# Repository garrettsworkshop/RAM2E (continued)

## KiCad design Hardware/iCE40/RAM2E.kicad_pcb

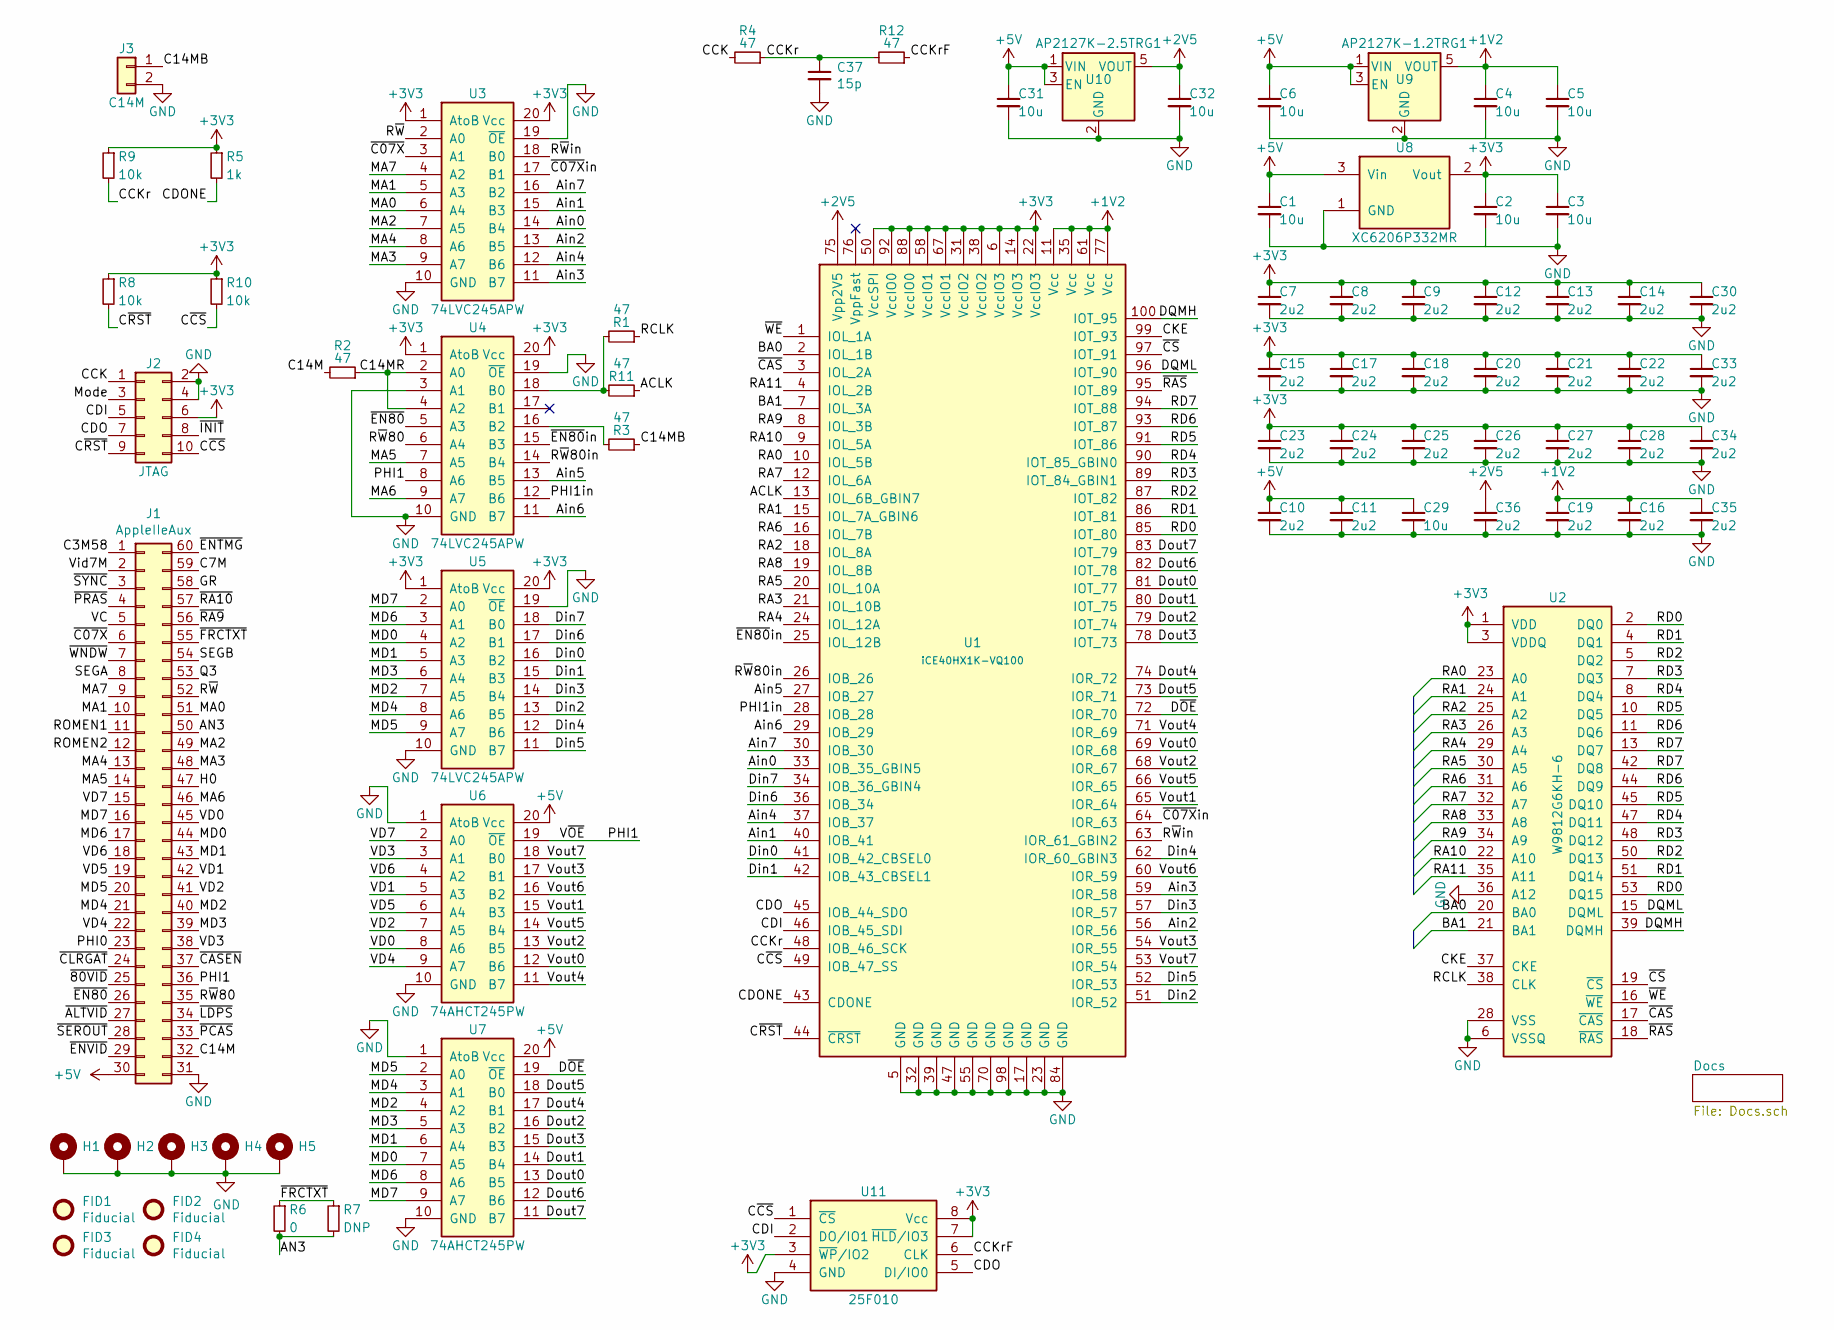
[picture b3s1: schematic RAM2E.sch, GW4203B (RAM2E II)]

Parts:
C1, C2, C3, C4, C5, C6, C29, C31, C32: 10u; C_0805; Mfg. Part Numbers Samsung CL21A106KAYNNNE; LCSC Part C15850
C7, C8, C9, C10, C11, C12, C13, C14, C15, C16, C17, C18, C19, C20, C21, C22, C23, C24, C25, C26, C27, C28, C30, C33, C34, C35, C36: 2u2; C_0603; Mfg. Part Numbers Samsung CL10A225KO8NNNC; LCSC Part C23630
C37: 15p; C_0603
FID1, FID2, FID3, FID4: Fiducial
H1, H2, H3, H4: PasteHole_1.152mm_NPTH
H5: PasteHole_1.1mm_PTH
J1: AppleIIeAux; AppleIIeAux_Edge
J2: JTAG; TC2050
J3: C14M; PinHeader_1x02_P2.54mm_Vertical
R1, R2, R3, R4, R11, R12: 47; R_0603; Mfg. Part Numbers Uniroyal 0603WAF470JT5E; LCSC Part C23182
R5: 1k; R_0603; Mfg. Part Numbers Uniroyal 0805W8F2202T5E; LCSC Part C17560
R6: 0; R_0805; Mfg. Part Numbers Uniroyal 0805W8F2202T5E; LCSC Part C17477
R7: DNP; R_0805
R8, R9, R10: 10k; R_0603; Mfg. Part Numbers Uniroyal 0805W8F2202T5E; LCSC Part C17560
U1: iCE40HX1K-VQ100; TQFP-100_14x14mm_P0.5mm
U2: W9812G6KH-6; TSOP-II-54_22.2x10.16mm_P0.8mm; Mfg. Part Numbers Winbond W9812G6KH-6, Winbond W9812G6KH-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; LCSC Part C62379
U3, U4, U5: 74LVC245APW; TSSOP-20_4.4x6.5mm_P0.65mm; Mfg. Part Numbers NXP 74LVC245APW, TI SN74LVC245APW; LCSC Part C6082
U6, U7: 74AHCT245PW; TSSOP-20_4.4x6.5mm_P0.65mm; Mfg. Part Numbers NXP 74AHCT245PW, TI SN74AHCT245PW; LCSC Part C173388
U8: XC6206P332MR; SOT-23; Mfg. Part Numbers Torex XC6206P332MR; LCSC Part C5446
U9: AP2127K-1.2TRG1; SOT-23-5
U10: AP2127K-2.5TRG1; SOT-23-5
U11: 25F010; SOIC-8_5.3mm

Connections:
+1V2: C4.1, C5.1, C16.1, C19.1, C35.1, U1.11 (Vcc), U1.35 (Vcc), U1.61 (Vcc), U1.77 (Vcc), U9.5 (VOUT)
+2V5: C32.1, C36.1, U1.75 (Vpp2V5), U10.5 (VOUT)
+3V3: C2.1, C3.1, C7.1, C8.1, C9.1, C12.1, C13.1, C14.1, C15.1, C17.1, C18.1, C20.1, C21.1, C22.1, C23.1, C24.1, C25.1, C26.1, C27.1, C28.1, C30.1, C33.1, C34.1, J2.6, R5.1, R8.1, R9.1, R10.1, U1.6 (VccIO3), U1.14 (VccIO3), U1.22 (VccIO3), U1.31 (VccIO2), U1.38 (VccIO2), U1.50 (VccSPI), U1.58 (VccIO1), U1.67 (VccIO1), U1.88 (VccIO0), U1.92 (VccIO0), U2.1 (VDD), U2.3 (VDDQ), U2.9 (VDDQ), U2.14 (VDD), U2.27 (VDD), U2.43 (VDDQ), U2.49 (VDDQ), U3.1 (AtoB), U3.20 (Vcc), U4.1 (AtoB), U4.20 (Vcc), U5.1 (AtoB), U5.20 (Vcc), U8.2 (Vout), U11.3 (~WP~/IO2), U11.7 (~HLD~/IO3), U11.8 (Vcc); also elsewhere on the board
+5V: C1.1, C6.1, C10.1, C11.1, C29.1, C31.1, J1.30, U6.20 (Vcc), U7.20 (Vcc), U8.3 (Vin), U9.1 (VIN), U9.3 (EN), U10.1 (VIN), U10.3 (EN)
/ACLK: R11.1, U1.13 (IOL_6B_GBIN7)
/AN3: J1.50, R6.2, R7.2
/Ain0: U1.33 (IOB_35_GBIN5), U3.14 (B4)
/Ain1: U1.40 (IOB_41), U3.15 (B3)
/Ain2: U1.56 (IOR_56), U3.13 (B5)
/Ain3: U1.59 (IOR_58), U3.11 (B7)
/Ain4: U1.37 (IOB_37), U3.12 (B6)
/Ain5: U1.27 (IOB_27), U4.13 (B5)
/Ain6: U1.29 (IOB_29), U4.11 (B7)
/Ain7: U1.30 (IOB_30), U3.16 (B2)
/BA0: U1.2 (IOL_1B), U2.20 (BA0)
/BA1: U1.7 (IOL_3A), U2.21 (BA1)
/C3M58: J1.1
/C7M: J1.59
/C14M: J1.32, R2.2
/C14MB: J3.1, R3.1
/C14MR: R2.1, U4.2 (A0), U4.4 (A2)
/CCK: J2.1, R4.2
/CCKr: C37.1, R4.1, R9.2, R12.2, U1.48 (IOB_46_SCK)
/CCKrF: R12.1, U11.6 (CLK)
/CDI: J2.5, U1.46 (IOB_45_SDI), U11.2 (DO/IO1)
/CDO: J2.7, U1.45 (IOB_44_SDO), U11.5 (DI/IO0)
/CDONE: R5.2, U1.43 (CDONE)
/CKE: U1.99 (IOT_93), U2.37 (CKE)
/C~CS~: J2.10, R10.2, U1.49 (IOB_47_SS), U11.1 (~CS~)
/C~RST~: J2.9, R8.2, U1.44 (~CRST~)
/DQMH: U1.100 (IOT_95), U2.39 (DQMH)
/DQML: U1.96 (IOT_90), U2.15 (DQML)
/Din0: U1.41 (IOB_42_CBSEL0), U5.16 (B2)
/Din1: U1.42 (IOB_43_CBSEL1), U5.15 (B3)
/Din2: U1.51 (IOR_52), U5.13 (B5)
/Din3: U1.57 (IOR_57), U5.14 (B4)
/Din4: U1.62 (IOR_60_GBIN3), U5.12 (B6)
/Din5: U1.52 (IOR_53), U5.11 (B7)
/Din6: U1.36 (IOB_34), U5.17 (B1)
/Din7: U1.34 (IOB_36_GBIN4), U5.18 (B0)
/Dout0: U1.81 (IOT_77), U7.13 (B5)
/Dout1: U1.80 (IOT_75), U7.14 (B4)
/Dout2: U1.79 (IOT_74), U7.16 (B2)
/Dout3: U1.78 (IOT_73), U7.15 (B3)
/Dout4: U1.74 (IOR_72), U7.17 (B1)
/Dout5: U1.73 (IOR_71), U7.18 (B0)
/Dout6: U1.82 (IOT_78), U7.12 (B6)
/Dout7: U1.83 (IOT_79), U7.11 (B7)
/GR: J1.58
/H0: J1.47
/MA0: J1.51, U3.6 (A4)
/MA1: J1.10, U3.5 (A3)
/MA2: J1.49, U3.7 (A5)
/MA3: J1.48, U3.9 (A7)
/MA4: J1.13, U3.8 (A6)
/MA5: J1.14, U4.7 (A5)
/MA6: J1.46, U4.9 (A7)
/MA7: J1.9, U3.4 (A2)
/MD0: J1.44, U5.4 (A2), U7.7 (A5)
/MD1: J1.43, U5.5 (A3), U7.6 (A4)
/MD2: J1.40, U5.7 (A5), U7.4 (A2)
/MD3: J1.39, U5.6 (A4), U7.5 (A3)
/MD4: J1.21, U5.8 (A6), U7.3 (A1)
/MD5: J1.20, U5.9 (A7), U7.2 (A0)
/MD6: J1.17, U5.3 (A1), U7.8 (A6)
/MD7: J1.16, U5.2 (A0), U7.9 (A7)
/Mode: J2.3
/PHI0: J1.23
/PHI1: J1.36, U4.8 (A6), U6.19 (~OE~)
/PHI1in: U1.28 (IOB_28), U4.12 (B6)
/Q3: J1.53
/RA0: U1.10 (IOL_5B), U2.23 (A0)
/RA1: U1.15 (IOL_7A_GBIN6), U2.24 (A1)
/RA2: U1.18 (IOL_8A), U2.25 (A2)
/RA3: U1.21 (IOL_10B), U2.26 (A3)
/RA4: U1.24 (IOL_12A), U2.29 (A4)
/RA5: U1.20 (IOL_10A), U2.30 (A5)
/RA6: U1.16 (IOL_7B), U2.31 (A6)
/RA7: U1.12 (IOL_6A), U2.32 (A7)
/RA8: U1.19 (IOL_8B), U2.33 (A8)
/RA9: U1.8 (IOL_3B), U2.34 (A9)
/RA10: U1.9 (IOL_5A), U2.22 (A10)
/RA11: U1.4 (IOL_2B), U2.35 (A11)
/RCLK: R1.1, U2.38 (CLK)
/RD0: U1.85 (IOT_80), U2.2 (DQ0), U2.53 (DQ15)
/RD1: U1.86 (IOT_81), U2.4 (DQ1), U2.51 (DQ14)
/RD2: U1.87 (IOT_82), U2.5 (DQ2), U2.50 (DQ13)
/RD3: U1.89 (IOT_84_GBIN1), U2.7 (DQ3), U2.48 (DQ12)
/RD4: U1.90 (IOT_85_GBIN0), U2.8 (DQ4), U2.47 (DQ11)
/RD5: U1.91 (IOT_86), U2.10 (DQ5), U2.45 (DQ10)
/RD6: U1.93 (IOT_87), U2.11 (DQ6), U2.44 (DQ9)
/RD7: U1.94 (IOT_88), U2.13 (DQ7), U2.42 (DQ8)
/ROMEN1: J1.11
/ROMEN2: J1.12
/R~W~: J1.52, U3.2 (A0)
/R~W~80: J1.35, U4.6 (A4); also elsewhere on the board
/R~W~80in: U1.26 (IOB_26), U4.14 (B4)
/R~W~in: U1.63 (IOR_61_GBIN2), U3.18 (B0)
/SEGA: J1.8
/SEGB: J1.54
/VC: J1.5
/VD0: J1.45, U6.8 (A6)
/VD1: J1.42, U6.5 (A3)
/VD2: J1.41, U6.7 (A5)
/VD3: J1.38, U6.3 (A1)
/VD4: J1.22, U6.9 (A7)
/VD5: J1.19, U6.6 (A4)
/VD6: J1.18, U6.4 (A2)
/VD7: J1.15, U6.2 (A0)
/Vid7M: J1.2
/Vout0: U1.69 (IOR_68), U6.12 (B6)
/Vout1: U1.65 (IOR_64), U6.15 (B3)
/Vout2: U1.68 (IOR_67), U6.13 (B5)
/Vout3: U1.54 (IOR_55), U6.17 (B1)
/Vout4: U1.71 (IOR_69), U6.11 (B7)
/Vout5: U1.66 (IOR_65), U6.14 (B4)
/Vout6: U1.60 (IOR_59), U6.16 (B2)
/Vout7: U1.53 (IOR_54), U6.18 (B0)
/~80VID~: J1.25
/~ALTVID~: J1.27
/~C07X~: J1.6, U3.3 (A1)
/~C07X~in: U1.64 (IOR_63), U3.17 (B1)
/~CASEN~: J1.37
/~CAS~: U1.3 (IOL_2A), U2.17 (~CAS~)
/~CLRGAT~: J1.24
/~CS~: U1.97 (IOT_91), U2.19 (~CS~)
/~EN80~: J1.26, U4.5 (A3); also elsewhere on the board
/~EN80~in: U1.25 (IOL_12B), U4.15 (B3)
/~ENTMG~: J1.60
/~ENVID~: J1.29
/~FRCTXT~: J1.55, R6.1, R7.1
/~INIT~: J2.8
/~LDPS~: J1.34
/~PCAS~: J1.33
/~PRAS~: J1.4
/~RA9~: J1.56
/~RA10~: J1.57
/~RAS~: U1.95 (IOT_89), U2.18 (~RAS~)
/~SEROUT~: J1.28
/~SYNC~: J1.3
/~WE~: U1.1 (IOL_1A), U2.16 (~WE~)
/~WNDW~: J1.7
GND: C1.2, C2.2, C3.2, C4.2, C5.2, C6.2, C7.2, C8.2, C9.2, C10.2, C11.2, C12.2, C13.2, C14.2, C15.2, C16.2, C17.2, C18.2, C19.2, C20.2, C21.2, C22.2, C23.2, C24.2, C25.2, C26.2, C27.2, C28.2, C29.2, C30.2, C31.2, C32.2, C33.2, C34.2, C35.2, C36.2, C37.2, H1.1, H2.1, H3.1, H4.1, H5.1, J1.31, J2.2, J2.4, J3.2, U1.5 (GND), U1.17 (GND), U1.23 (GND), U1.32 (GND), U1.39 (GND), U1.47 (GND), U1.55 (GND), U1.70 (GND), U1.84 (GND), U1.98 (GND), U2.6 (VSSQ), U2.12 (VSSQ), U2.28 (VSS), U2.36 (A12), U2.41 (VSS), U2.46 (VSSQ), U2.52 (VSSQ), U2.54 (VSS), U3.10 (GND), U3.19 (~OE~), U4.3 (A1), U4.10 (GND), U4.19 (~OE~), U5.10 (GND), U5.19 (~OE~), U6.1 (AtoB), U6.10 (GND), U7.1 (AtoB), U7.10 (GND), U8.1 (GND), U9.2 (GND), U10.2 (GND), U11.4 (GND); also elsewhere on the board
unnamed: R1.2, R11.2, U4.18 (B0)
unnamed: R3.2, U4.16 (B2)

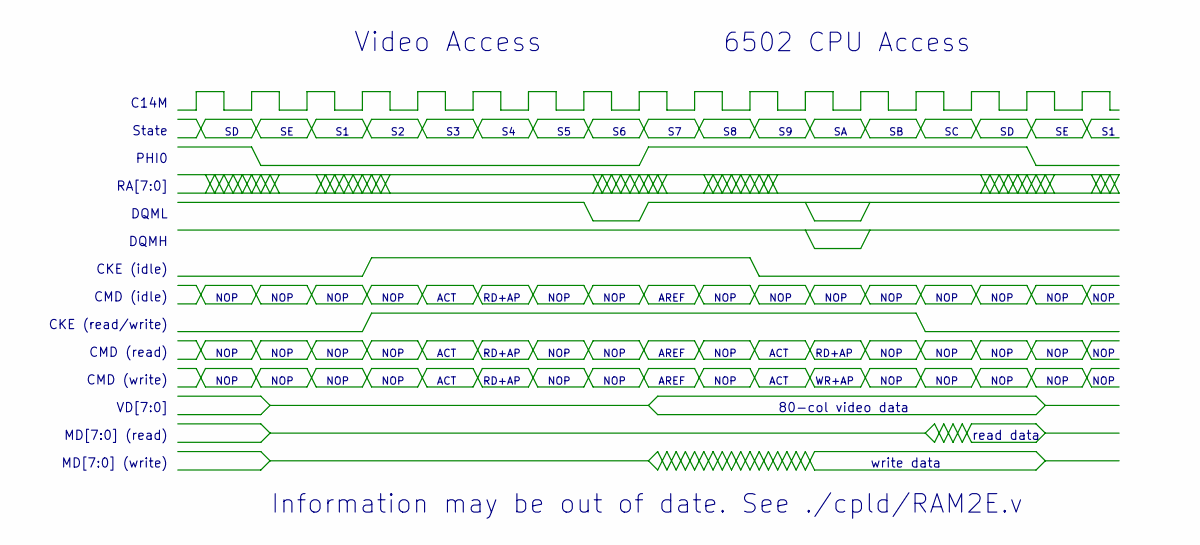
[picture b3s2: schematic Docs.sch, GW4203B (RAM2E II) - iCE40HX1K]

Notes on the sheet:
Video Access
6502 CPU Access
PHI0
C14M
RA[7:0]
State
CKE (read/write)
NOP
RD+AP
ACT
WR+AP
CMD (write)
CMD (read)
DQML
VD[7:0]
MD[7:0] (read)
MD[7:0] (write)
Information may be out of date. See ./cpld/RAM2E.v
read data
write data
80-col video data
CMD (idle)
CKE (idle)
AREF
DQMH

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
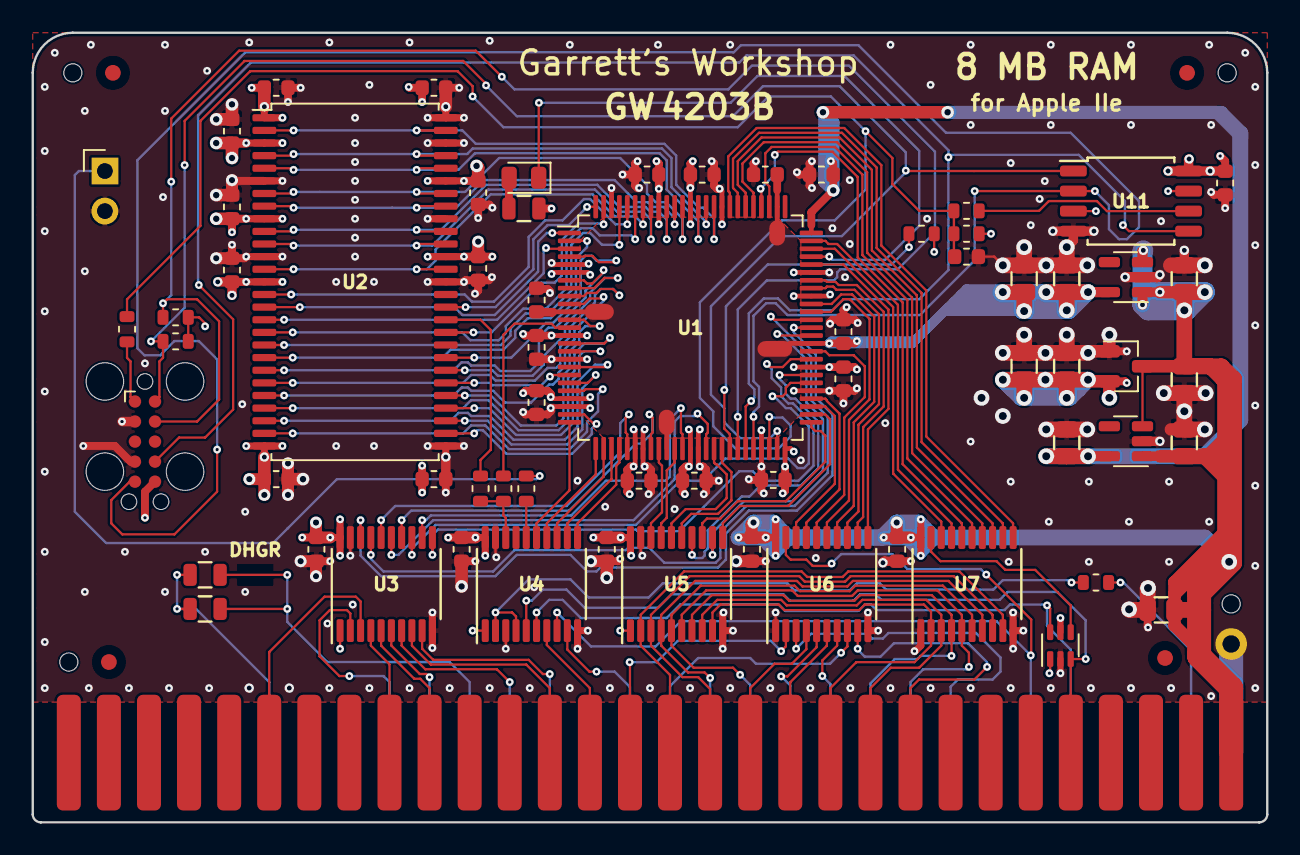
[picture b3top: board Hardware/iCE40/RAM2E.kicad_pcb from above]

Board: 4 copper layers, 78.2 x 50.0 mm, 75 parts (0 on the bottom side), 120 nets.

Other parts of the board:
D1: White; LED_0805
R13: 180; R_0805
U12: 74LVC1G97; SOT-363

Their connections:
+3V3: R13.2, U12.1, U12.5; also elsewhere on the board
/R~W~80: U12.6; also elsewhere on the board
/~EN80~: U12.3; also elsewhere on the board
GND: U12.2; also elsewhere on the board
unnamed: D1.2, R13.1

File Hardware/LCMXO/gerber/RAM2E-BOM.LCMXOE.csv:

Reference, Quantity, Value, Footprint, Datasheet, LCSC Part, Mfg. Part Numbers, Notes
C7 C8 C9 C10 C11 C12 C13 C14 C15 C16 C17 C18 C19 C20 C21 C22 C23 C24 C25 C26 C27 C28 C30 ,23,2u2,stdpads:C_0603,,C23630,Samsung CL10A225KO8NNNC,"10V or higher. Any manufacturer's part is acceptable but Samsung, Murata, Yageo preferred."
C1 C2 C3 C4 C5 C6 C29 ,7,10u,stdpads:C_0805,,C15850,Samsung CL21A106KAYNNNE,"10V or higher. Any manufacturer's part is acceptable but Samsung, Murata, Yageo preferred."
C31 ,1,15p,stdpads:C_0603,,,,"10V or higher. Any manufacturer's part is acceptable but Samsung, Murata, Yageo preferred."
D1 ,1,White,stdpads:LED_0805,,C34499,Hubei Kento C34499,Any manufacturer's part is acceptable.
FID1 FID2 FID3 FID4 ,4,Fiducial,stdpads:Fiducial,,,,DNP - SMT vision system fiducial
H1 H2 H3 H4 ,4, ,stdpads:PasteHole_1.152mm_NPTH,,,,DNP - mounting hole for solder paste printing
H5 ,1, ,stdpads:PasteHole_1.1mm_PTH,,,,DNP - mounting hole
J1 ,1,AppleIIeAux,stdpads:AppleIIeAux_Edge,,,,DNP - edge connector
J2 ,1,JTAG,stdpads:TC2050,,,,DNP - test pad connector
J3 ,1,C14M,Connector_PinHeader_2.54mm:PinHeader_1x02_P2.54mm_Vertical,,,,DNP
R1 ,1,DNP,stdpads:R_0805,,,,
R10 ,1,180,stdpads:R_0805,,C25270,Uniroyal 0805W8F1800T5E,Any manufacturer's part is acceptable.
R2 R3 R4 R5 R8 ,5,47,stdpads:R_0603,,C23182,Uniroyal 0603WAF470JT5E,Any manufacturer's part is acceptable.
R6 ,1,0,stdpads:R_0805,,C17477,Uniroyal 0805W8F0000T5E,Any manufacturer's part is acceptable.
R7 ,1,DNP,stdpads:R_0805,,,,
R9 ,1,10k,stdpads:R_0603,,C25804,Uniroyal 0603WAF1002T5E,Any manufacturer's part is acceptable.
U1 ,1,LCMXO256-TN100,stdpads:TQFP-100_14x14mm_P0.5mm,,C1550734,"Lattice LCMXO256E-3TN100C, Lattice LCMXO256E-4TN100C, Lattice LCMXO256E-5TN100C, Lattice LCMXO256E-3TN100I, Lattice LCMXO256E-4TN100I, Lattice LCMXO640E-3TN100C, Lattice LCMXO640E-4TN100C, Lattice LCMXO640E-5TN100C, Lattice LCMXO640E-3TN100I, Lattice LCMXO640E-4TN100I",
U11 ,1,25F010,stdpads:SOIC-8_5.3mm,,C2687406,"Zetta ZD25WD20BTIGT, Adesto AT25SF081-SSHD, Winbond W25X20CLSNIG",Most SPI flash in SOIC-8 (3.9mm / 150 mil width) package is acceptable.
U2 ,1,W9812G6KH-6,stdpads:TSOP-II-54_22.2x10.16mm_P0.8mm,,C62379,"Winbond W9812G6KH-6, Winbond W9812G6KH-6I, Winbond W9825G6KH-6, Winbond W9825G6KH-6I, ISSI IS42S16160J-6TL, ISSI IS42S16160J-6TLI, Micron MT48LC16M16A2P-6A :G, Micron MT48LC16M16A2P-6A IT:G",Most 166 MHz 128/256 Mbit x16 SDRAM is acceptable.
U3 U4 U5 ,3,74LVC245APW,stdpads:TSSOP-20_4.4x6.5mm_P0.65mm,,C6082,"NXP 74LVC245APW, TI SN74LVC245APW, NXP 74AHC245PW, NXP 74AHC245APW, TI SN74AHC245PW",Most 74LVC245 or 74AHC245 in TSSOP-20 package is acceptable.
U6 U7 ,2,74AHCT245PW,stdpads:TSSOP-20_4.4x6.5mm_P0.65mm,,C173388,"NXP 74AHCT245PW, NXP 74AHCT245APW, TI SN74AHCT245PW",Most 74AHCT245 in TSSOP-20 package is acceptable.
U8 ,1,XC6206P332MR,stdpads:SOT-23,,C5446,Torex XC6206P332MR,Most 3.3V regulator in SOT-23 package is acceptable.
U9 ,1,AP2127K-1.2TRG1,stdpads:SOT-23-5,,C151376,"Diodes AP2127K-1.2TRG1, Torex XC6228D122VR",Most 1.2V regulator in SOT-23-5 package is acceptable.

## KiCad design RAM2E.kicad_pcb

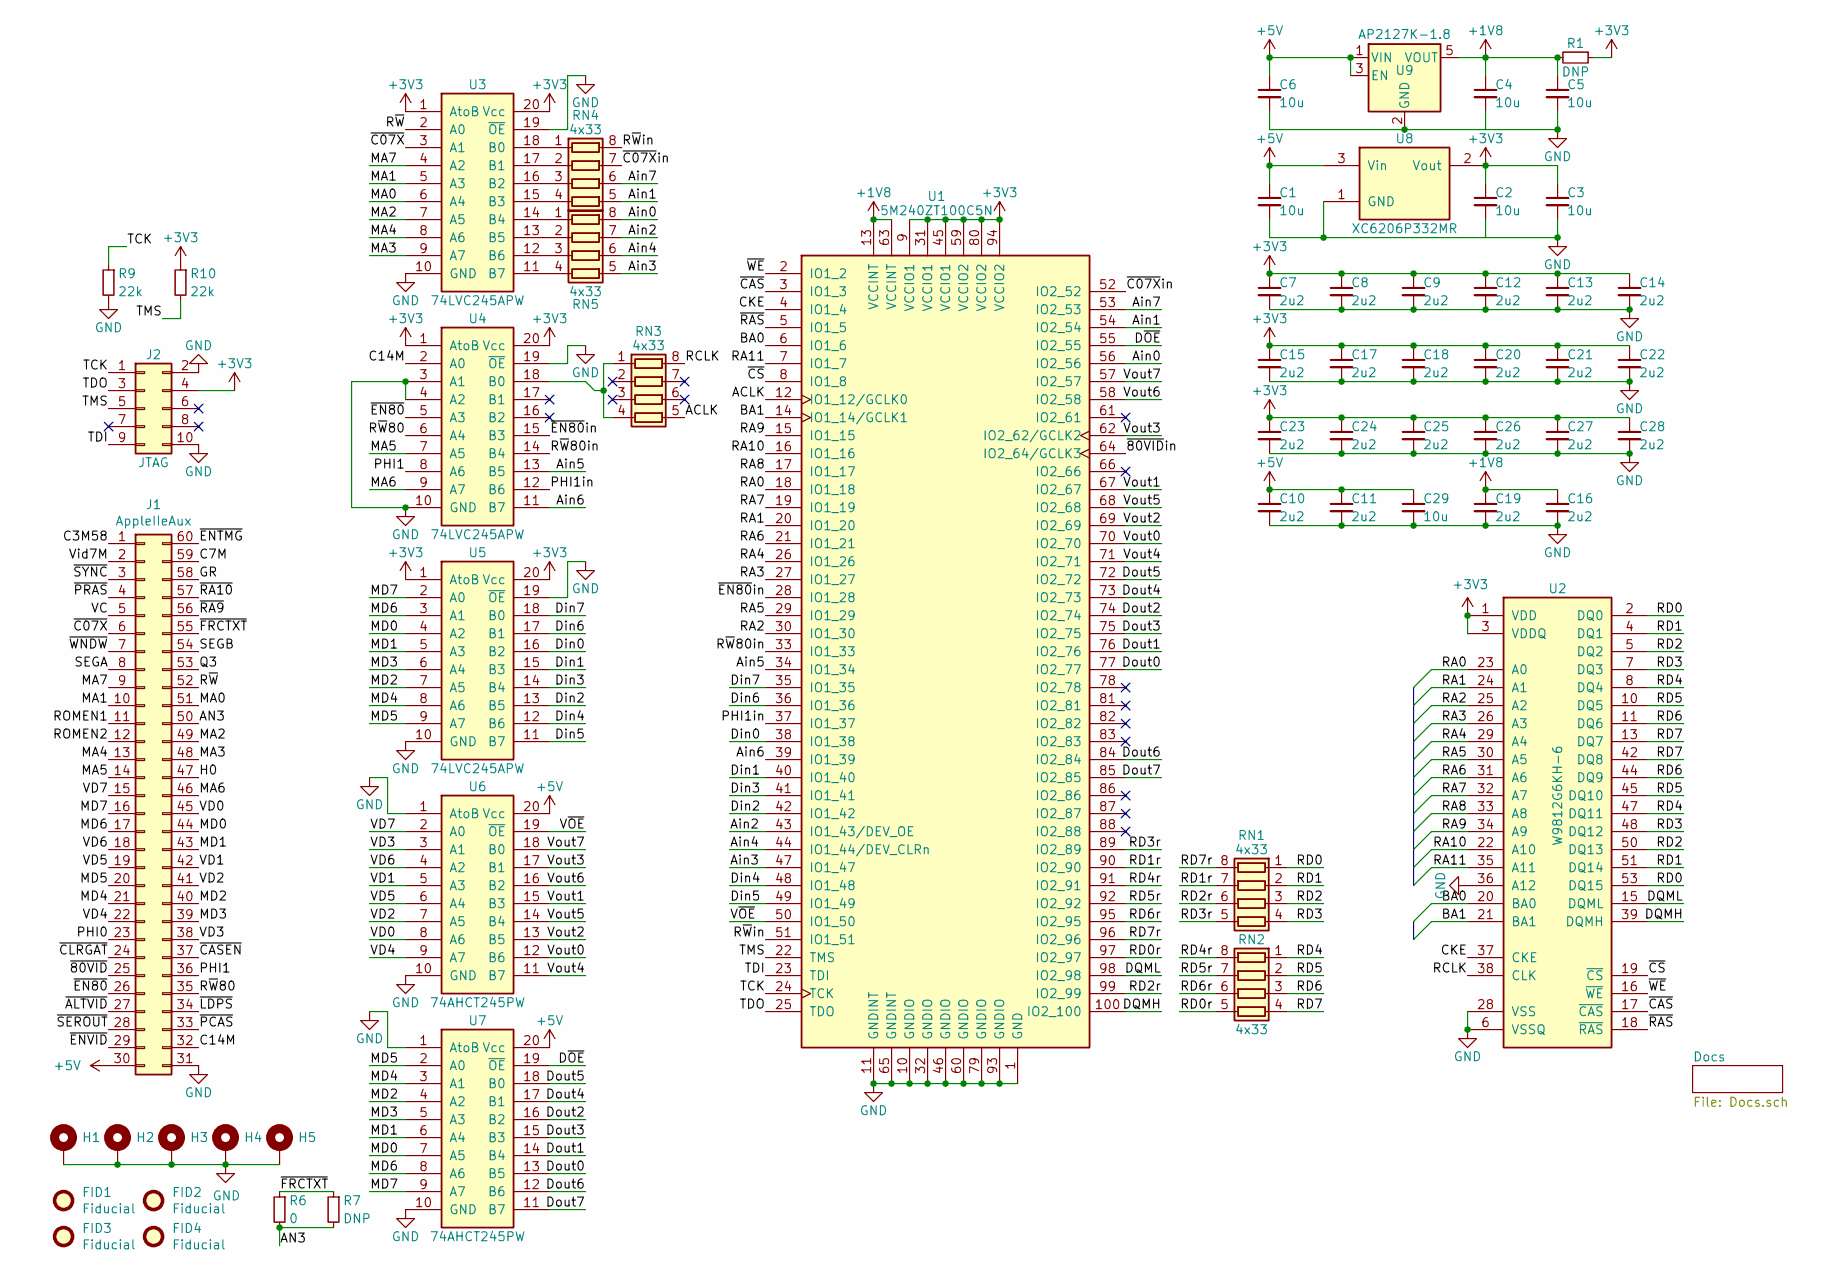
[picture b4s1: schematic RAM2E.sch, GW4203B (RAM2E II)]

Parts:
C1, C2, C3, C4, C5, C6, C29: 10u; C_0805; LCSC Part C15850
C7, C8, C9, C10, C11, C12, C13, C14, C15, C16, C17, C18, C19, C20, C21, C22, C23, C24, C25, C26, C27, C28: 2u2; C_0603; LCSC Part C23630
FID1, FID2, FID3, FID4: Fiducial
H1, H2, H3, H4: PasteHole_1.152mm_NPTH
H5: PasteHole_1.1mm_PTH
J1: AppleIIeAux; AppleIIeAux_Edge
J2: JTAG; TC2050
R1, R7: DNP; R_0805
R6: 0; R_0805; LCSC Part C17477
R9, R10: 22k; R_0805; LCSC Part C17560
RN1, RN2, RN3, RN4, RN5: 4x33; R4_0402; LCSC Part C25501
U1: 5M240ZT100C5N; TQFP-100_14x14mm_P0.5mm; LCSC Part C192889
U2: W9812G6KH-6; TSOP-II-54_22.2x10.16mm_P0.8mm; LCSC Part C62379
U3, U4, U5: 74LVC245APW; TSSOP-20_4.4x6.5mm_P0.65mm; LCSC Part C6082
U6, U7: 74AHCT245PW; TSSOP-20_4.4x6.5mm_P0.65mm; LCSC Part C173388
U8: XC6206P332MR; SOT-23; LCSC Part C5446
U9: AP2127K-1.8; SOT-23-5; LCSC Part C151375

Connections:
+1V8: C4.1, C5.1, C16.1, C19.1, R1.2, U1.13 (VCCINT), U1.63 (VCCINT), U9.5 (VOUT)
+3V3: C2.1, C3.1, C7.1, C8.1, C9.1, C12.1, C13.1, C14.1, C15.1, C17.1, C18.1, C20.1, C21.1, C22.1, C23.1, C24.1, C25.1, C26.1, C27.1, C28.1, J2.4, R1.1, R10.1, U1.9 (VCCIO1), U1.31 (VCCIO1), U1.45 (VCCIO1), U1.59 (VCCIO2), U1.80 (VCCIO2), U1.94 (VCCIO2), U2.1 (VDD), U2.3 (VDDQ), U2.9 (VDDQ), U2.14 (VDD), U2.27 (VDD), U2.43 (VDDQ), U2.49 (VDDQ), U3.1 (AtoB), U3.20 (Vcc), U4.1 (AtoB), U4.20 (Vcc), U5.1 (AtoB), U5.20 (Vcc), U8.2 (Vout)
+5V: C1.1, C6.1, C10.1, C11.1, C29.1, J1.30, U6.20 (Vcc), U7.20 (Vcc), U8.3 (Vin), U9.1 (VIN), U9.3 (EN)
/ACLK: RN3.5 (R4.2), U1.12 (IO1_12/GCLK0)
/AN3: J1.50, R6.2, R7.2
/Ain0: RN5.8 (R1.2), U1.56 (IO2_56)
/Ain1: RN4.5 (R4.2), U1.54 (IO2_54)
/Ain2: RN5.7 (R2.2), U1.43 (IO1_43/DEV_OE)
/Ain3: RN5.5 (R4.2), U1.47 (IO1_47)
/Ain4: RN5.6 (R3.2), U1.44 (IO1_44/DEV_CLRn)
/Ain5: U1.34 (IO1_34), U4.13 (B5)
/Ain6: U1.39 (IO1_39), U4.11 (B7)
/Ain7: RN4.6 (R3.2), U1.53 (IO2_53)
/BA0: U1.6 (IO1_6), U2.20 (BA0)
/BA1: U1.14 (IO1_14/GCLK1), U2.21 (BA1)
/C3M58: J1.1
/C7M: J1.59
/C14M: J1.32, U4.2 (A0)
/CKE: U1.4 (IO1_4), U2.37 (CKE)
/DQMH: U1.100 (IO2_100), U2.39 (DQMH)
/DQML: U1.98 (IO2_98), U2.15 (DQML)
/Din0: U1.38 (IO1_38), U5.16 (B2)
/Din1: U1.40 (IO1_40), U5.15 (B3)
/Din2: U1.42 (IO1_42), U5.13 (B5)
/Din3: U1.41 (IO1_41), U5.14 (B4)
/Din4: U1.48 (IO1_48), U5.12 (B6)
/Din5: U1.49 (IO1_49), U5.11 (B7)
/Din6: U1.36 (IO1_36), U5.17 (B1)
/Din7: U1.35 (IO1_35), U5.18 (B0)
/Dout0: U1.77 (IO2_77), U7.13 (B5)
/Dout1: U1.76 (IO2_76), U7.14 (B4)
/Dout2: U1.74 (IO2_74), U7.16 (B2)
/Dout3: U1.75 (IO2_75), U7.15 (B3)
/Dout4: U1.73 (IO2_73), U7.17 (B1)
/Dout5: U1.72 (IO2_72), U7.18 (B0)
/Dout6: U1.84 (IO2_84), U7.12 (B6)
/Dout7: U1.85 (IO2_85), U7.11 (B7)
/D~OE~: U1.55 (IO2_55), U7.19 (~OE~)
/GR: J1.58
/H0: J1.47
/MA0: J1.51, U3.6 (A4)
/MA1: J1.10, U3.5 (A3)
/MA2: J1.49, U3.7 (A5)
/MA3: J1.48, U3.9 (A7)
/MA4: J1.13, U3.8 (A6)
/MA5: J1.14, U4.7 (A5)
/MA6: J1.46, U4.9 (A7)
/MA7: J1.9, U3.4 (A2)
/MD0: J1.44, U5.4 (A2), U7.7 (A5)
/MD1: J1.43, U5.5 (A3), U7.6 (A4)
/MD2: J1.40, U5.7 (A5), U7.4 (A2)
/MD3: J1.39, U5.6 (A4), U7.5 (A3)
/MD4: J1.21, U5.8 (A6), U7.3 (A1)
/MD5: J1.20, U5.9 (A7), U7.2 (A0)
/MD6: J1.17, U5.3 (A1), U7.8 (A6)
/MD7: J1.16, U5.2 (A0), U7.9 (A7)
/PHI0: J1.23
/PHI1: J1.36, U4.8 (A6)
/PHI1in: U1.37 (IO1_37), U4.12 (B6)
/Q3: J1.53
/RA0: U1.18 (IO1_18), U2.23 (A0)
/RA1: U1.20 (IO1_20), U2.24 (A1)
/RA2: U1.30 (IO1_30), U2.25 (A2)
/RA3: U1.27 (IO1_27), U2.26 (A3)
/RA4: U1.26 (IO1_26), U2.29 (A4)
/RA5: U1.29 (IO1_29), U2.30 (A5)
/RA6: U1.21 (IO1_21), U2.31 (A6)
/RA7: U1.19 (IO1_19), U2.32 (A7)
/RA8: U1.17 (IO1_17), U2.33 (A8)
/RA9: U1.15 (IO1_15), U2.34 (A9)
/RA10: U1.16 (IO1_16), U2.22 (A10)
/RA11: U1.7 (IO1_7), U2.35 (A11)
/RCLK: RN3.8 (R1.2), U2.38 (CLK)
/RD0: RN1.1 (R1.1), U2.2 (DQ0), U2.53 (DQ15)
/RD0r: RN2.5 (R4.2), U1.97 (IO2_97)
/RD1: RN1.2 (R2.1), U2.4 (DQ1), U2.51 (DQ14)
/RD1r: RN1.7 (R2.2), U1.90 (IO2_90)
/RD2: RN1.3 (R3.1), U2.5 (DQ2), U2.50 (DQ13)
/RD2r: RN1.6 (R3.2), U1.99 (IO2_99)
/RD3: RN1.4 (R4.1), U2.7 (DQ3), U2.48 (DQ12)
/RD3r: RN1.5 (R4.2), U1.89 (IO2_89)
/RD4: RN2.1 (R1.1), U2.8 (DQ4), U2.47 (DQ11)
/RD4r: RN2.8 (R1.2), U1.91 (IO2_91)
/RD5: RN2.2 (R2.1), U2.10 (DQ5), U2.45 (DQ10)
/RD5r: RN2.7 (R2.2), U1.92 (IO2_92)
/RD6: RN2.3 (R3.1), U2.11 (DQ6), U2.44 (DQ9)
/RD6r: RN2.6 (R3.2), U1.95 (IO2_95)
/RD7: RN2.4 (R4.1), U2.13 (DQ7), U2.42 (DQ8)
/RD7r: RN1.8 (R1.2), U1.96 (IO2_96)
/ROMEN1: J1.11
/ROMEN2: J1.12
/R~W~: J1.52, U3.2 (A0)
/R~W~80: J1.35, U4.6 (A4)
/R~W~80in: U1.33 (IO1_33), U4.14 (B4)
/R~W~in: RN4.8 (R1.2), U1.51 (IO1_51)
/SEGA: J1.8
/SEGB: J1.54
/TCK: J2.1, R9.1, U1.24 (TCK)
/TDI: J2.9, U1.23 (TDI)
/TDO: J2.3, U1.25 (TDO)
/TMS: J2.5, R10.2, U1.22 (TMS)
/VC: J1.5
/VD0: J1.45, U6.8 (A6)
/VD1: J1.42, U6.5 (A3)
/VD2: J1.41, U6.7 (A5)
/VD3: J1.38, U6.3 (A1)
/VD4: J1.22, U6.9 (A7)
/VD5: J1.19, U6.6 (A4)
/VD6: J1.18, U6.4 (A2)
/VD7: J1.15, U6.2 (A0)
/Vid7M: J1.2
/Vout0: U1.70 (IO2_70), U6.12 (B6)
/Vout1: U1.67 (IO2_67), U6.15 (B3)
/Vout2: U1.69 (IO2_69), U6.13 (B5)
/Vout3: U1.62 (IO2_62/GCLK2), U6.17 (B1)
/Vout4: U1.71 (IO2_71), U6.11 (B7)
/Vout5: U1.68 (IO2_68), U6.14 (B4)
/Vout6: U1.58 (IO2_58), U6.16 (B2)
/Vout7: U1.57 (IO2_57), U6.18 (B0)
/V~OE~: U1.50 (IO1_50), U6.19 (~OE~)
/~80VID~: J1.25
/~80VID~in: U1.64 (IO2_64/GCLK3)
/~ALTVID~: J1.27
/~C07X~: J1.6, U3.3 (A1)
/~C07X~in: RN4.7 (R2.2), U1.52 (IO2_52)
/~CASEN~: J1.37
/~CAS~: U1.3 (IO1_3), U2.17 (~CAS~)
/~CLRGAT~: J1.24
/~CS~: U1.8 (IO1_8), U2.19 (~CS~)
/~EN80~: J1.26, U4.5 (A3)
/~EN80~in: U1.28 (IO1_28), U4.15 (B3)
/~ENTMG~: J1.60
/~ENVID~: J1.29
/~FRCTXT~: J1.55, R6.1, R7.1
/~LDPS~: J1.34
/~PCAS~: J1.33
/~PRAS~: J1.4
/~RA9~: J1.56
/~RA10~: J1.57
/~RAS~: U1.5 (IO1_5), U2.18 (~RAS~)
/~SEROUT~: J1.28
/~SYNC~: J1.3
/~WE~: U1.2 (IO1_2), U2.16 (~WE~)
/~WNDW~: J1.7
GND: C1.2, C2.2, C3.2, C4.2, C5.2, C6.2, C7.2, C8.2, C9.2, C10.2, C11.2, C12.2, C13.2, C14.2, C15.2, C16.2, C17.2, C18.2, C19.2, C20.2, C21.2, C22.2, C23.2, C24.2, C25.2, C26.2, C27.2, C28.2, C29.2, H1.1, H2.1, H3.1, H4.1, H5.1, J1.31, J2.2, J2.10, R9.2, U1.1 (GND), U1.10 (GNDIO), U1.11 (GNDINT), U1.32 (GNDIO), U1.46 (GNDIO), U1.60 (GNDIO), U1.65 (GNDINT), U1.79 (GNDIO), U1.93 (GNDIO), U2.6 (VSSQ), U2.12 (VSSQ), U2.28 (VSS), U2.36 (A12), U2.41 (VSS), U2.46 (VSSQ), U2.52 (VSSQ), U2.54 (VSS), U3.10 (GND), U3.19 (~OE~), U4.3 (A1), U4.4 (A2), U4.10 (GND), U4.19 (~OE~), U5.10 (GND), U5.19 (~OE~), U6.1 (AtoB), U6.10 (GND), U7.1 (AtoB), U7.10 (GND), U8.1 (GND), U9.2 (GND)
unnamed: RN3.1 (R1.1), RN3.4 (R4.1), U4.18 (B0)
unnamed: RN4.1 (R1.1), U3.18 (B0)
unnamed: RN4.2 (R2.1), U3.17 (B1)
unnamed: RN4.3 (R3.1), U3.16 (B2)
unnamed: RN4.4 (R4.1), U3.15 (B3)
unnamed: RN5.1 (R1.1), U3.14 (B4)
unnamed: RN5.2 (R2.1), U3.13 (B5)
unnamed: RN5.3 (R3.1), U3.12 (B6)
unnamed: RN5.4 (R4.1), U3.11 (B7)

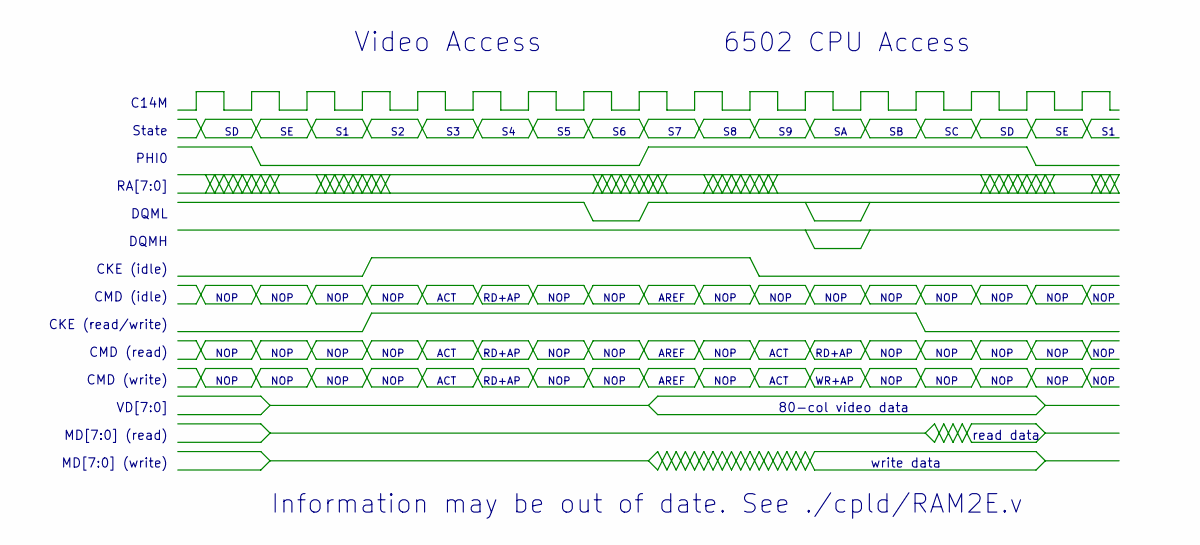
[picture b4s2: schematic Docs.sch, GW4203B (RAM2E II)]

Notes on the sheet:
Video Access
6502 CPU Access
PHI0
C14M
RA[7:0]
State
CKE (read/write)
NOP
RD+AP
ACT
WR+AP
CMD (write)
CMD (read)
DQML
VD[7:0]
MD[7:0] (read)
MD[7:0] (write)
Information may be out of date. See ./cpld/RAM2E.v
read data
write data
80-col video data
CMD (idle)
CKE (idle)
AREF
DQMH

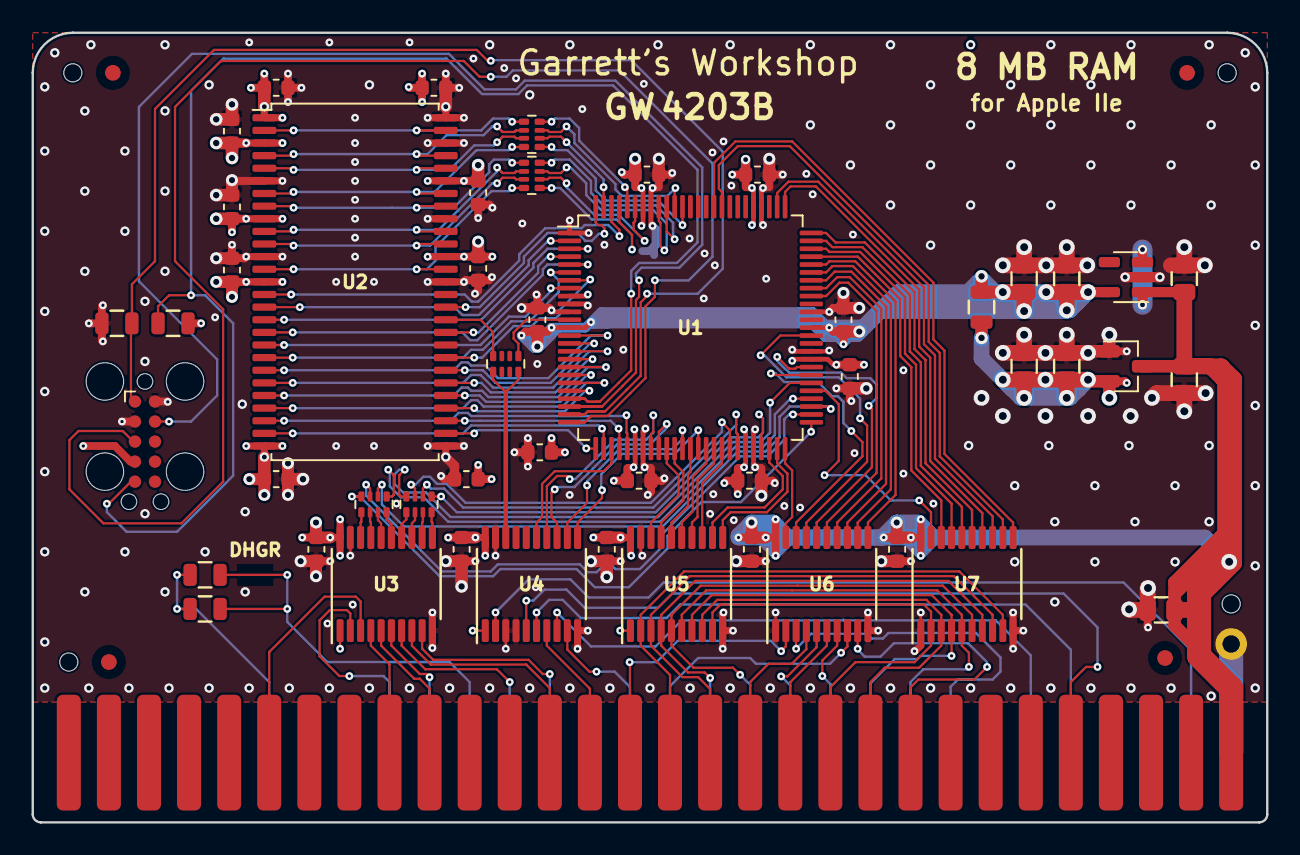
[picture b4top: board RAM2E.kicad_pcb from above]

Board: 4 copper layers, 78.2 x 50.0 mm, 59 parts (0 on the bottom side), 127 nets.

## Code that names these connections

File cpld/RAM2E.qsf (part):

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set_global_assignment -name FLOW_ENABLE_POWER_ANALYZER OFF
set_global_assignment -name POWER_DEFAULT_INPUT_IO_TOGGLE_RATE "12.5 %"

set_location_assignment PIN_12 -to C14M
set_instance_assignment -name IO_STANDARD "3.3-V LVCMOS" -to C14M
set_instance_assignment -name WEAK_PULL_UP_RESISTOR OFF -to C14M

set_location_assignment PIN_37 -to PHI1
set_instance_assignment -name IO_STANDARD "3.3-V LVCMOS" -to PHI1
set_instance_assignment -name PAD_TO_CORE_DELAY 1 -to PHI1
set_instance_assignment -name WEAK_PULL_UP_RESISTOR OFF -to PHI1
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set_instance_assignment -name FAST_OUTPUT_REGISTER ON -to Vout
set_instance_assignment -name WEAK_PULL_UP_RESISTOR OFF -to Vout

set_location_assignment PIN_4 -to CKE
set_instance_assignment -name IO_STANDARD "3.3-V LVCMOS" -to CKE
set_instance_assignment -name CURRENT_STRENGTH_NEW "MINIMUM CURRENT" -to CKE
set_instance_assignment -name SLOW_SLEW_RATE ON -to CKE
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set_instance_assignment -name FAST_OUTPUT_REGISTER ON -to RA
set_instance_assignment -name WEAK_PULL_UP_RESISTOR OFF -to RA

set_location_assignment PIN_100 -to DQMH
set_instance_assignment -name IO_STANDARD "3.3-V LVCMOS" -to DQMH
set_instance_assignment -name CURRENT_STRENGTH_NEW "MINIMUM CURRENT" -to DQMH
set_instance_assignment -name SLOW_SLEW_RATE ON -to DQMH
set_instance_assignment -name FAST_OUTPUT_REGISTER ON -to DQMH
set_instance_assignment -name WEAK_PULL_UP_RESISTOR OFF -to DQMH

set_location_assignment PIN_98 -to DQML
set_instance_assignment -name IO_STANDARD "3.3-V LVCMOS" -to DQML
set_instance_assignment -name CURRENT_STRENGTH_NEW "MINIMUM CURRENT" -to DQML
set_instance_assignment -name SLOW_SLEW_RATE ON -to DQML
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
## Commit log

2020-07-25 Create LICENSE
2020-07-25 Add GW4203A files
2020-07-25 Add GW4203B files
2020-07-31 Documentation update
2020-07-31 Fixed typo in manual
2020-08-03 Documentaton update
2020-08-05 As submitted to JLCPCB August 2020
2020-08-05 Added MS Word "~$" temporary file to gitignore
2020-08-05 Update GW4203BManual
2020-08-08 August 2020 JLCPCB again
2020-08-21 As submitted to JLCPCB August 21 2020
2020-09-09 Working on MAX V
2020-09-10 Updated schematic with 1V8 regulator and MAX V
2020-09-11 Updated pictures
2020-09-11 Actually put the right pictures
2020-09-16 Improve power consumption
    Gated RAM access during PHI0, squeezed video access and MPU access together, gated data bus output buffer OE to only output at end of PHI0
2020-09-17 Fix snow on screen
    Previous commit had "snow" in 80-col mode when updating display. Put back command timing to fix problem. Kept PHI0 read gating depending on EN80 and data output gating
2020-09-25 Update timing diagram in schematic
    Now reflects longer MAX V propagation delays
2020-09-29 Fabbed 9/29/2020
2020-10-09 Actually fabbed 10/6/2020
2020-12-16 Added C14M buffering and header
2020-12-25 Fabbed
2020-12-26 Increased refresh frequency
2021-01-28 Refresh rate increase compiled in Quartus
2021-01-28 Gitignore Quartus CDFs (chain definition files)
2021-02-16 Add MAX V BOM and placement table
2021-03-11 Rename /cpld directory to /cpld_maxii
2021-03-11 Added MAX V CPLD firmware
2021-03-11 Removed old MAX II stuff from MAX V directory
2021-04-03 Add dev note
2021-04-03 Remove dev note stuff from manual
2021-04-03 Add transparent isometric front image
2021-05-08 started
2021-05-22 still workin
2021-06-01 Generated gerbers and documentation
2021-06-01 Fixed DRC violations on LCMXO2 and iCE40 boards
2021-06-01 DNP 3d models and add FrontIsom render pics of all board variants
2021-06-01 BOM finished
2021-06-01 Zip everything
2021-06-01 Add stencil zip files
2023-09-21 Remove old files
2023-09-21 Fixed MachXO board wrong JTAG pinout
2023-11-03 2.1?
2023-11-07 Update Makefile
2023-11-11 Fixed LED and current-limiting resistor values in BOM
2023-11-21 As sent to testers
2023-12-18 Revert "As sent to testers"
    This reverts commit aa65c256270fe6ff4ce89bd299c66a1d149a4454.
2023-12-18 Revert "As sent to testers"
    This reverts commit 4249ebe98332ad6fb679362fa153720a3e50f79b.
2023-12-27 Init sequence clears first 2048 bytes of first two RAMWorks banks
2023-12-27 Refactor to separate core and chip-specific stuff
2024-01-11 MAX II/V 2.1 RC1
2024-01-19 fix comment
2024-01-19 Fix comments
2024-01-19 Add back qws files
2024-01-27 nVOE change
2024-01-31 Change BOM to separate U4 from U3 and U5
2024-01-31 change nVOE to be solely falling-edge register output
2024-02-08 Small board revision, still v2.0
2024-02-08 Firmware RC
2024-02-15 Just formatting changes, MAX II/V POF files identical
2024-04-16 Update Makefile to add BOM generation
2024-04-24 RC 2.1
2024-04-24 Remove C14M header 3d model
2024-04-24 RC
    Fix board IDs
2024-05-20 Update Makefile to change to C revision naming
2024-07-20 GW4203C.1.0 RC3
2025-02-15 RC C.1.1
